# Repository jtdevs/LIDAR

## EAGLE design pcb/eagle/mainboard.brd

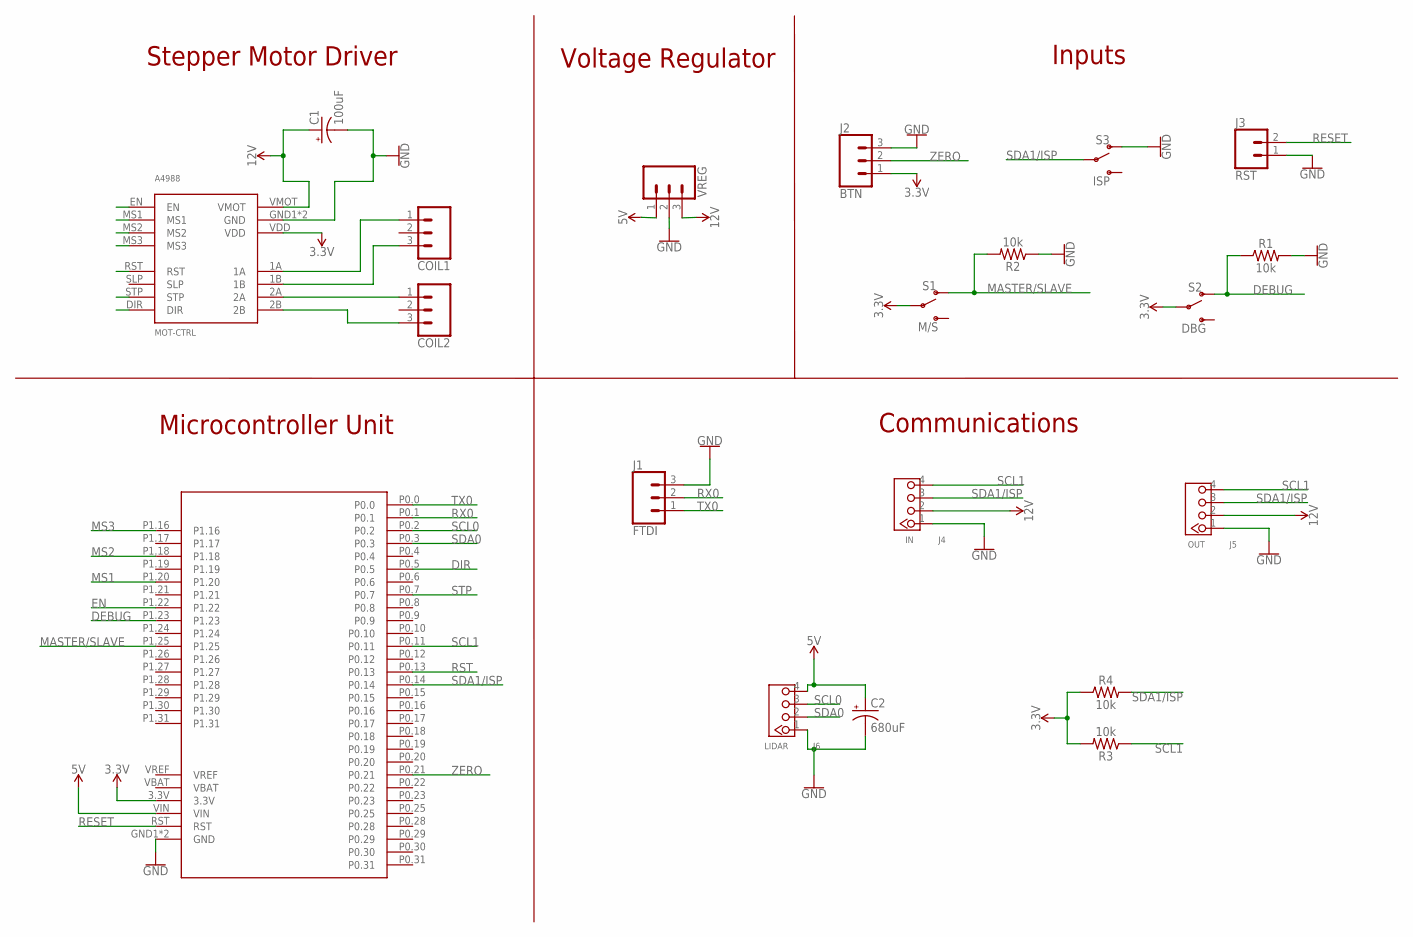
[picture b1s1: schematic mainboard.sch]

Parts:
A4988: MOT-CTRL; POLOLU-6X8
C1: 100uF; CPOL-RADIAL-2.5MM-6.5MM
C2: 680uF; CPOL-RADIAL-2.5MM-6.5MM
COIL1, COIL2: CONN_03-SCREW-5MM; SCREWTERMINAL-5MM-3
J1: FTDI; 1X03
J2: BTN; 1X03
J3: RST; 1X02
J4: IN; HW4-2.0
J5: OUT; HW4-2.0
J6: LIDAR; HW4-2.0
LPC2148: MCU; LPC-H2148
R1, R2, R3, R4: 10k; AXIAL-0.3
S1: M/S; SWITCH_SPDT_PTH_11.6X4.0MM
S2: DBG; SWITCH_SPDT_PTH_11.6X4.0MM
S3: ISP; SWITCH_SPDT_PTH_11.6X4.0MM
VREG: CONN_03; 1X03

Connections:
3.3V: A4988.VDD, J2.1, LPC2148.3.3V, R3.P$2 (2), R4.P$1 (1), S1.2, S2.2
5V: C2.1 (+), J6.4, LPC2148.VIN, VREG.1
12V: A4988.VMOT, C1.1 (+), J4.2, J5.2, VREG.3
DEBUG: LPC2148.P1.23, R1.P$1 (1), S2.1 (O)
DIR: A4988.DIR, LPC2148.P0.5
EN: A4988.EN, LPC2148.P1.22
GND: A4988.GND1 (GND), A4988.GND2 (GND), C1.2 (-), C2.2 (-), J1.3, J2.3, J3.1, J4.1, J5.1, J6.1, LPC2148.GND1 (GND), LPC2148.GND2 (GND), R1.P$2 (2), R2.P$1 (1), S3.1 (O), VREG.2
MASTER/SLAVE: LPC2148.P1.25, R2.P$2 (2), S1.1 (O)
MS1: A4988.MS1, LPC2148.P1.20
MS2: A4988.MS2, LPC2148.P1.18
MS3: A4988.MS3, LPC2148.P1.16
unnamed: A4988.2B, COIL2.3
unnamed: A4988.2A, COIL2.1
unnamed: A4988.1B, COIL1.3
unnamed: A4988.1A, COIL1.1
RESET: J3.2, LPC2148.RST
RST: A4988.RST, LPC2148.P0.13
RX0: J1.2, LPC2148.P0.1
SCL0: J6.3, LPC2148.P0.2
SCL1: J4.4, J5.4, LPC2148.P0.11, R3.P$1 (1)
SDA0: J6.2, LPC2148.P0.3
SDA1/ISP: J4.3, J5.3, LPC2148.P0.14, R4.P$2 (2), S3.2
STP: A4988.STP, LPC2148.P0.7
TX0: J1.1, LPC2148.P0.0
ZERO: J2.2, LPC2148.P0.21

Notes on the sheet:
Stepper Motor Driver
Microcontroller Unit
Inputs
Communications
Voltage Regulator

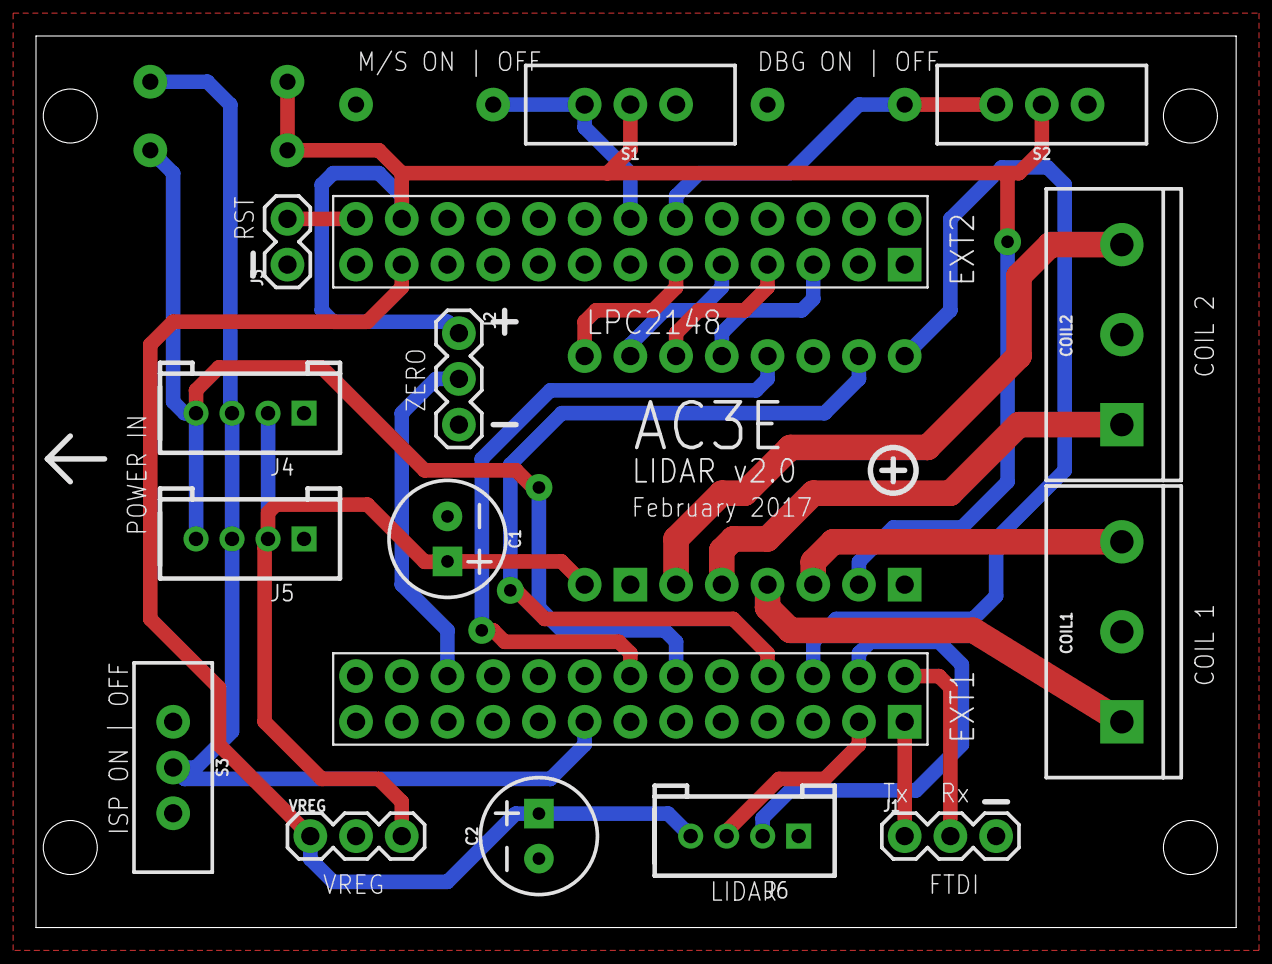
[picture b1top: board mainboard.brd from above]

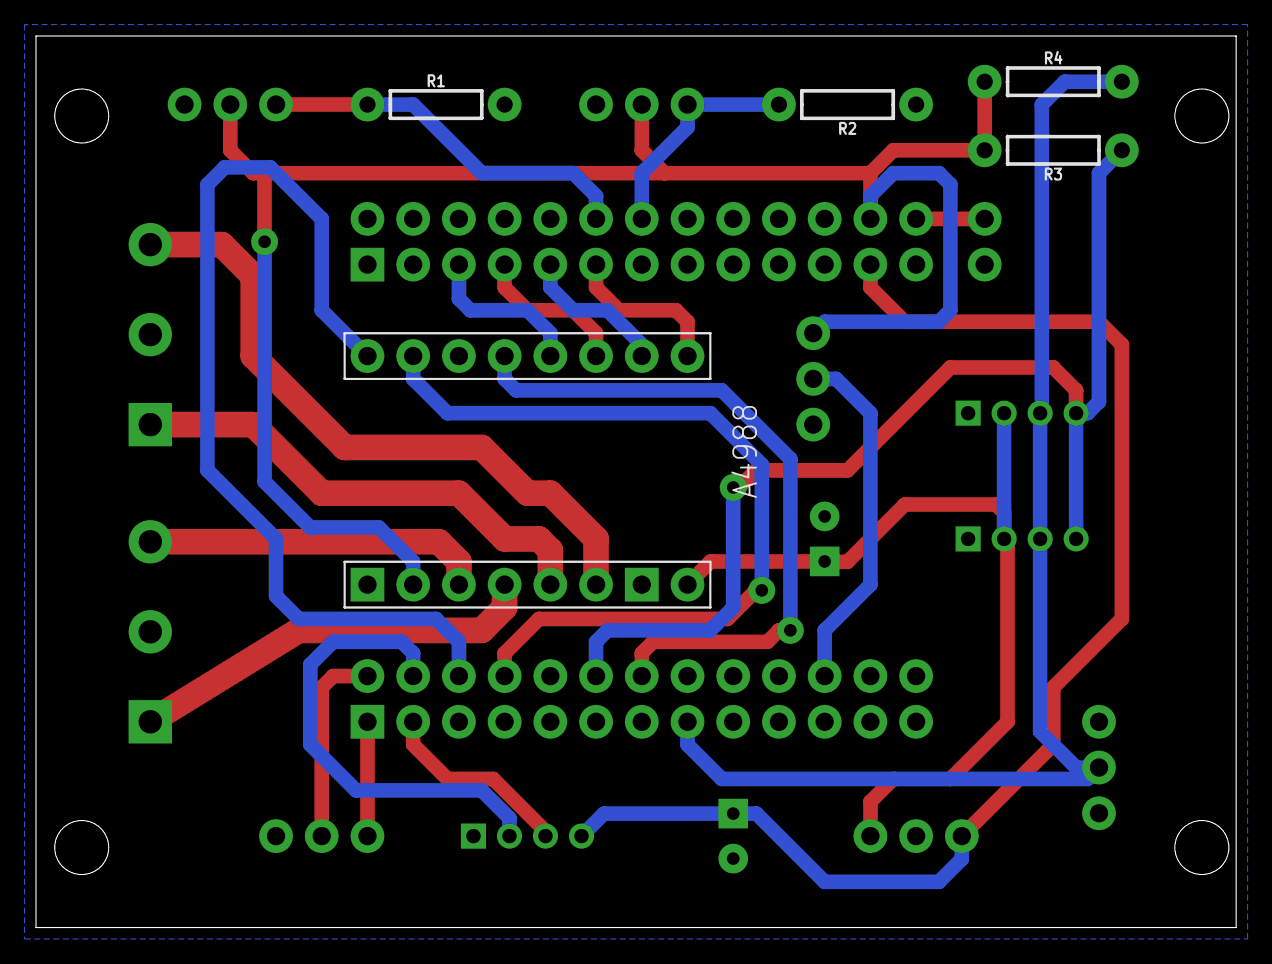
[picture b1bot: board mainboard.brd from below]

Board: 2 copper layers, 66.7 x 49.5 mm, 20 parts (5 on the bottom side), 25 nets.

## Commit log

2017-06-10 Iteration #1 after huge changes
    Errors found:
    pointer pinput not initialized was causing the system to be unresponsive to I2C commands. Everything else looks fine so far.
    Minor changes in code style.
    Interface code updated to match the changes in the system logic.
2017-06-10 last build: 9/6/17 20:30
2017-06-10 saved it in a new folder
2017-06-10 Iteration #2 of 9/6/17
    Rookie mistake, wasn't sending the pointcloud after receiving it.... LOL
2017-06-10 Bug found and detailed in main
2017-06-12 Index problem solved
2017-07-14 uvision setup + test
2017-07-14 UART interrupt routine
2017-07-14 continuos scan test

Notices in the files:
parts and their libraries:
SparkFun-Capacitors: Licensing: Creative Commons ShareAlike 4.0 International - https://creativecommons.org/licenses/by-sa/4.0
